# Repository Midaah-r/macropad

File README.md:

# Macropad - Slickopad

*A fully custom 12 key macropad with a small oled panel and a rotary encoder!*

## Gallery  

### **PCB & Electronics**  
| Schematic | PCB | Assembled (front)| Assembled (back |  
|-----------|-----|-----------|----------------| 
|  |  |  |   |  

### **Case Components**  
| Top Case (Angle 1) | Top Case ( Angle 2) | Bottom Case (Angle 1) | Bottom Case (Angle 2) | Plate |  
|------------------|--------------------|-------------|-------| --------|
|  |  |  |  |  |  

### **Assembly**  

This was my first somewhat complex pcb build along with my first time using CAD. 

I've not made (gpt'd) the firmware completely and ill set it up completely when the macropad is physically present.

## Features 
- 8 degree incline
- Oled panel
- Rotary encoder for volume/brightness/etc
- 3 function layers (the 3 right keys)

PS: i had to compromise on the switching functionality of the RE because i couldnt accomodate the its pins due to insufficient gpio pins in the MCU.  didnt want to compromise the design and decided to go ahead with this.

## Design  
- White case
- Black plate
- Black keycaps
- Black knob
  
## Dimensions
- Top plate: **7mm**
- Plate: **1.5mm**
- Base: **13.5mm**
- Inclination bottom block: max height **14mm**

- Total height (main body): **21mm**
- Total height (max): **36mm**

---

### Materials  
| Component | Qty |  
|-----------|-----|  
| DSA keycaps | 12x |  
| MX switches | 12x |    
| XIAO RP2040 | 1x |  
| M3×16 bolts | 4x |  
| EC11 encoder | 1x |
| Oled panel-SSD1306 (0.91') | 1x|
| Knob | 1x |  
| PCB | 1x |
| Case | 1x |

---

> **Note:** Print case parts in white; PCB must be black.

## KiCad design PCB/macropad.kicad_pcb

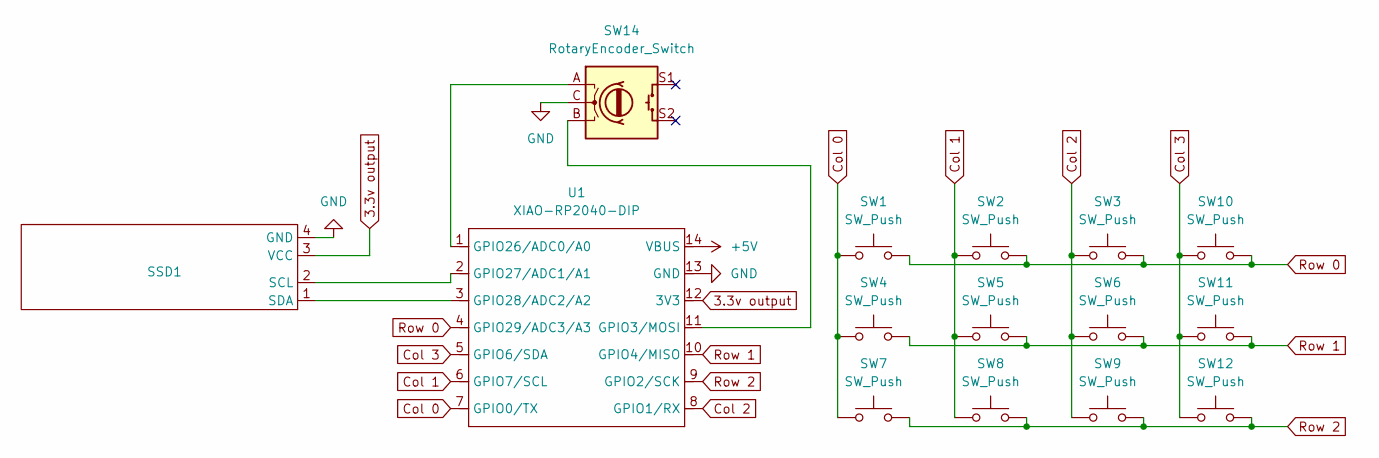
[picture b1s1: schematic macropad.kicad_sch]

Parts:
SSD1: SSD1306-0.91-OLED-4pin-128x32
SW1, SW2, SW3, SW4, SW5, SW6, SW7, SW8, SW9, SW10, SW11, SW12: SW_Push; SW_Cherry_MX_1.00u_PCB
SW14: RotaryEncoder_Switch; RotaryEncoder_Alps_EC11E-Switch_Vertical_H20mm_CircularMoun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
U1: XIAO-RP2040-DIP

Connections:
3.3v output: SSD1.3 (VCC), U1.12 (3V3)
+5V: U1.14 (VBUS)
Col 0: SW1.1, SW4.1, SW7.1, U1.7 (GPIO0/TX)
Col 1: SW2.1, SW5.1, SW8.1, U1.6 (GPIO7/SCL)
Col 2: SW3.1, SW6.1, SW9.1, U1.8 (GPIO1/RX)
Col 3: SW10.1, SW11.1, SW12.1, U1.5 (GPIO6/SDA)
GND: SSD1.4 (GND), SW14.C, U1.13 (GND)
unnamed: SSD1.2 (SCL), U1.2 (GPIO27/ADC1/A1)
unnamed: SSD1.1 (SDA), U1.3 (GPIO28/ADC2/A2)
unnamed: SW14.B, U1.11 (GPIO3/MOSI)
unnamed: SW14.A, U1.1 (GPIO26/ADC0/A0)
Row 0: SW1.2, SW2.2, SW3.2, SW10.2, U1.4 (GPIO29/ADC3/A3)
Row 1: SW4.2, SW5.2, SW6.2, SW11.2, U1.10 (GPIO4/MISO)
Row 2: SW7.2, SW8.2, SW9.2, SW12.2, U1.9 (GPIO2/SCK)

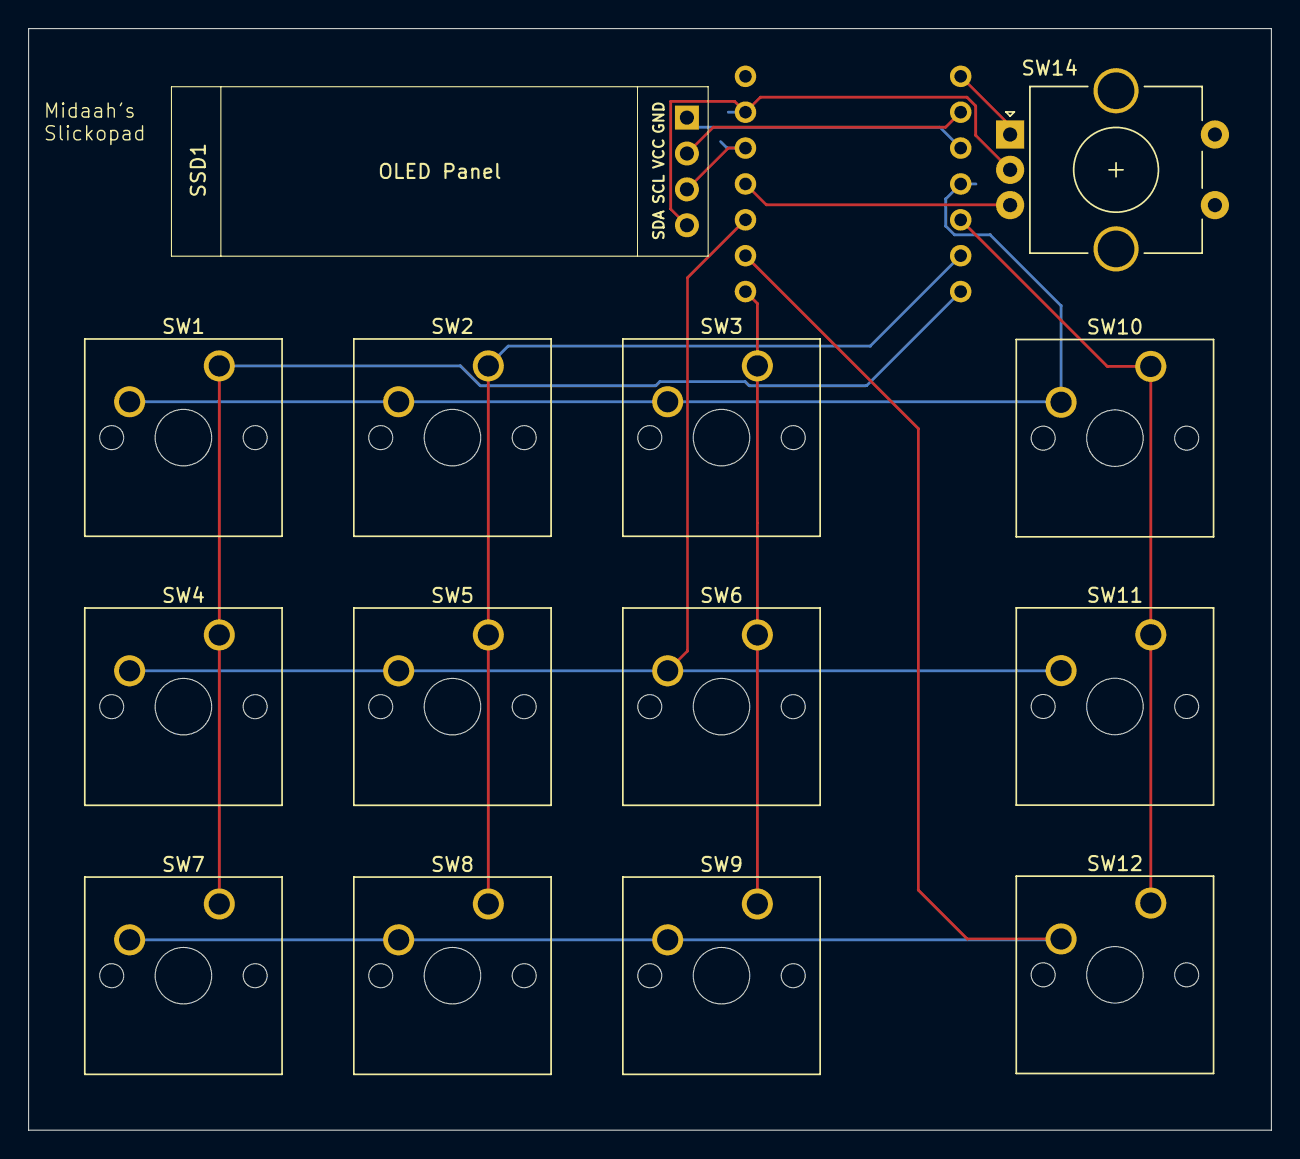
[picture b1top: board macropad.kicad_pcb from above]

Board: 2 copper layers, 88.0 x 78.0 mm, 15 parts (1 on the bottom side), 13 nets.

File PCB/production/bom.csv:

Designator,Footprint,Quantity,Value,LCSC Part #
SSD1,SSD1306-0.91-OLED-4pin-128x32,1,~,
"SW1, SW10, SW11, SW12, SW2, SW3, SW4, SW5, SW6, SW7, SW8, SW9",SW_Cherry_MX_1.00u_PCB,12,SW_Push,
SW14,RotaryEncoder_Alps_EC11E-Switch_Vertical_H20mm_CircularMountingHoles,1,RotaryEncoder_Switch,
U1,XIAO-RP2040-DIP,1,XIAO-RP2040-DIP,

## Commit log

2025-07-30 added assets folder
2025-07-30 updated assets
2025-07-30 added partial firmware
2025-07-30 Added CAD, PCB and Production
